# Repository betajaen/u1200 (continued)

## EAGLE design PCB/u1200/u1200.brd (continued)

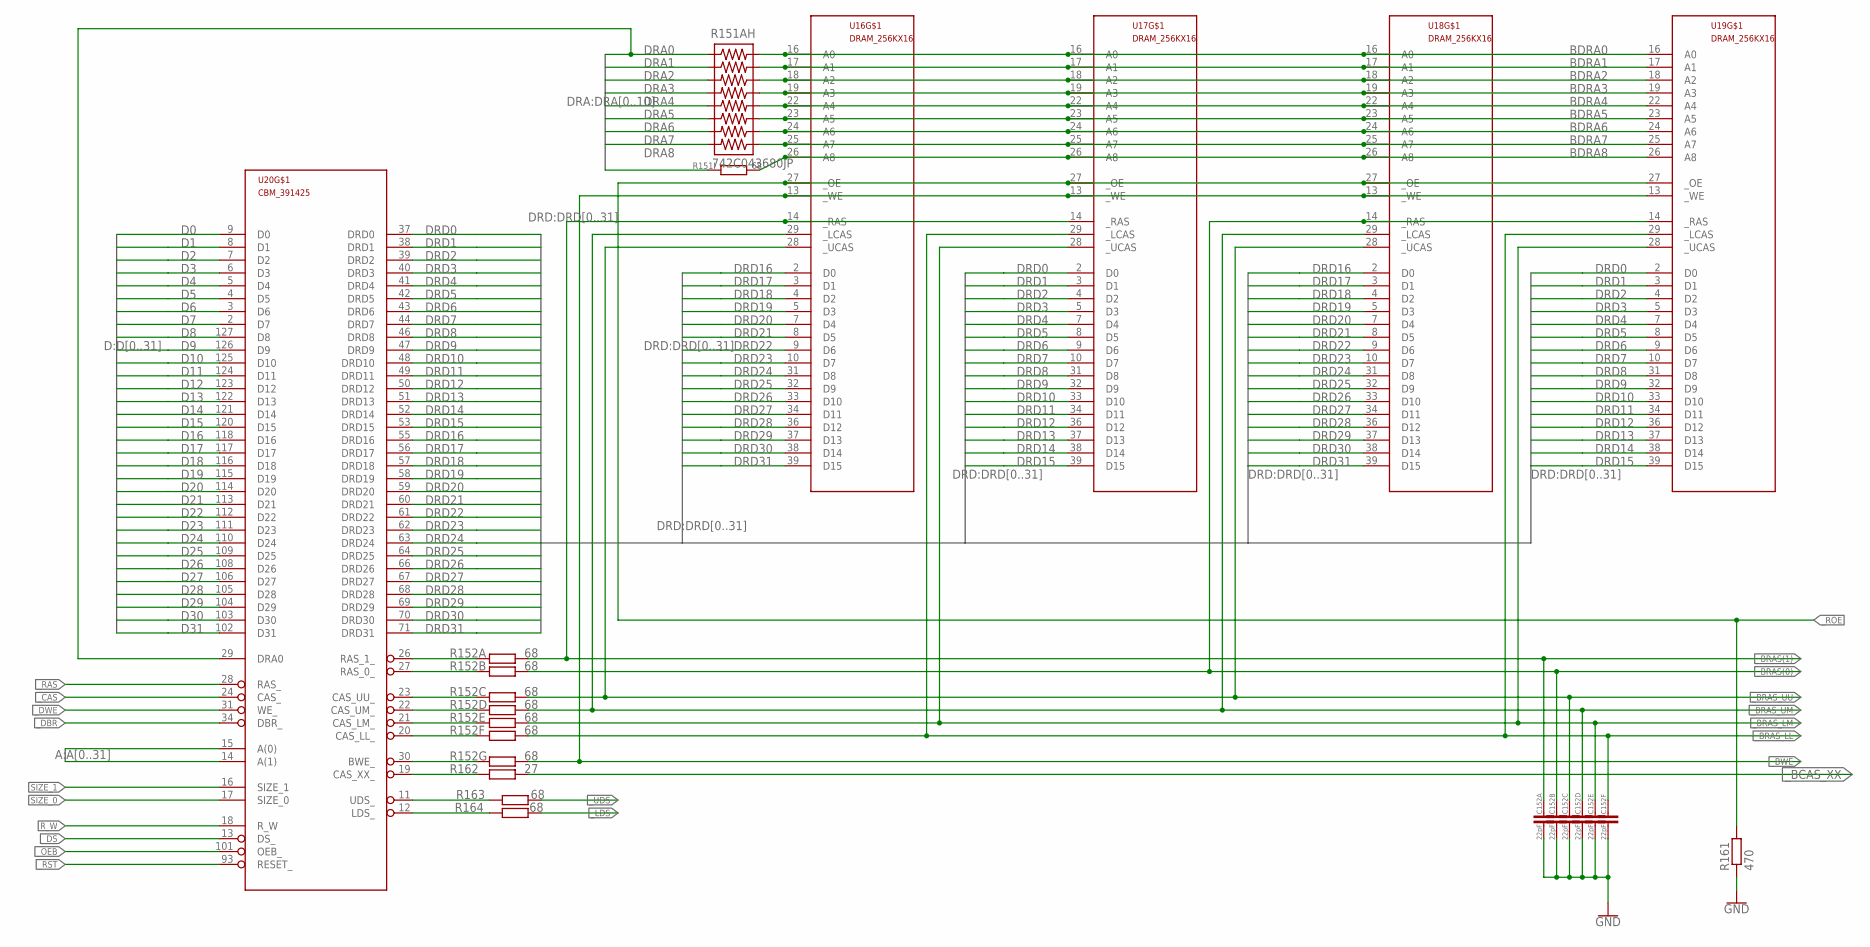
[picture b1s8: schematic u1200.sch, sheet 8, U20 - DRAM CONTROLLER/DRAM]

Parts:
C152A, C152B, C152C, C152D, C152E, C152F: 22pF; C0805
R151AH: 742C043680JP; 742C163220JP; MPN 742C043680JP; DIGIKEY_PARTNO 742C043680JPTR-ND
R151I: 68; R0603
R152A, R152B, R152C, R152D, R152E, R152F, R152G, R163, R164: 68; R0805
R161: 470; R0805
R162: 27; R0805
U16, U17, U18, U19: DRAM_256KX16; SOJ127P1117X376-40
U20: CBM_391425; SQFP-S-28X28-128

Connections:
A0: U20.15 (A(0)); also elsewhere on the board
A1: U20.14 (A(1)); also elsewhere on the board
BDRA0: R151AH.16, U16.16 (A0), U17.16 (A0), U18.16 (A0), U19.16 (A0)
BDRA1: R151AH.15, U16.17 (A1), U17.17 (A1), U18.17 (A1), U19.17 (A1)
BDRA2: R151AH.14, U16.18 (A2), U17.18 (A2), U18.18 (A2), U19.18 (A2)
BDRA3: R151AH.13, U16.19 (A3), U17.19 (A3), U18.19 (A3), U19.19 (A3)
BDRA4: R151AH.12, U16.22 (A4), U17.22 (A4), U18.22 (A4), U19.22 (A4)
BDRA5: R151AH.11, U16.23 (A5), U17.23 (A5), U18.23 (A5), U19.23 (A5)
BDRA6: R151AH.10, U16.24 (A6), U17.24 (A6), U18.24 (A6), U19.24 (A6)
BDRA7: R151AH.9, U16.25 (A7), U17.25 (A7), U18.25 (A7), U19.25 (A7)
BDRA8: R151I.2, U16.26 (A8), U17.26 (A8), U18.26 (A8), U19.26 (A8)
D0: U20.9 (D0); also elsewhere on the board
D1: U20.8 (D1); also elsewhere on the board
D2: U20.7 (D2); also elsewhere on the board
D3: U20.6 (D3); also elsewhere on the board
D4: U20.5 (D4); also elsewhere on the board
D5: U20.4 (D5); also elsewhere on the board
D6: U20.3 (D6); also elsewhere on the board
D7: U20.2 (D7); also elsewhere on the board
D8: U20.127 (D8); also elsewhere on the board
D9: U20.126 (D9); also elsewhere on the board
D10: U20.125 (D10); also elsewhere on the board
D11: U20.124 (D11); also elsewhere on the board
D12: U20.123 (D12); also elsewhere on the board
D13: U20.122 (D13); also elsewhere on the board
D14: U20.121 (D14); also elsewhere on the board
D15: U20.120 (D15); also elsewhere on the board
D16: U20.118 (D16); also elsewhere on the board
D17: U20.117 (D17); also elsewhere on the board
D18: U20.116 (D18); also elsewhere on the board
D19: U20.115 (D19); also elsewhere on the board
D20: U20.114 (D20); also elsewhere on the board
D21: U20.113 (D21); also elsewhere on the board
D22: U20.112 (D22); also elsewhere on the board
D23: U20.111 (D23); also elsewhere on the board
D24: U20.110 (D24); also elsewhere on the board
D25: U20.109 (D25); also elsewhere on the board
D26: U20.108 (D26); also elsewhere on the board
D27: U20.106 (D27); also elsewhere on the board
D28: U20.105 (D28); also elsewhere on the board
D29: U20.104 (D29); also elsewhere on the board
D30: U20.103 (D30); also elsewhere on the board
D31: U20.102 (D31); also elsewhere on the board
DRA0: R151AH.1, U20.29 (DRA0); also elsewhere on the board
DRA1: R151AH.2; also elsewhere on the board
DRA2: R151AH.3; also elsewhere on the board
DRA3: R151AH.4; also elsewhere on the board
DRA4: R151AH.5; also elsewhere on the board
DRA5: R151AH.6; also elsewhere on the board
DRA6: R151AH.7; also elsewhere on the board
DRA7: R151AH.8; also elsewhere on the board
DRA8: R151I.1; also elsewhere on the board
DRD0: U17.2 (D0), U19.2 (D0), U20.37 (DRD0); also elsewhere on the board
DRD1: U17.3 (D1), U19.3 (D1), U20.38 (DRD1); also elsewhere on the board
DRD2: U17.4 (D2), U19.4 (D2), U20.39 (DRD2); also elsewhere on the board
DRD3: U17.5 (D3), U19.5 (D3), U20.40 (DRD3); also elsewhere on the board
DRD4: U17.7 (D4), U19.7 (D4), U20.41 (DRD4); also elsewhere on the board
DRD5: U17.8 (D5), U19.8 (D5), U20.42 (DRD5); also elsewhere on the board
DRD6: U17.9 (D6), U19.9 (D6), U20.43 (DRD6); also elsewhere on the board
DRD7: U17.10 (D7), U19.10 (D7), U20.44 (DRD7); also elsewhere on the board
DRD8: U17.31 (D8), U19.31 (D8), U20.46 (DRD8); also elsewhere on the board
DRD9: U17.32 (D9), U19.32 (D9), U20.47 (DRD9); also elsewhere on the board
DRD10: U17.33 (D10), U19.33 (D10), U20.48 (DRD10); also elsewhere on the board
DRD11: U17.34 (D11), U19.34 (D11), U20.49 (DRD11); also elsewhere on the board
DRD12: U17.36 (D12), U19.36 (D12), U20.50 (DRD12); also elsewhere on the board
DRD13: U17.37 (D13), U19.37 (D13), U20.51 (DRD13); also elsewhere on the board
DRD14: U17.38 (D14), U19.38 (D14), U20.52 (DRD14); also elsewhere on the board
DRD15: U17.39 (D15), U19.39 (D15), U20.53 (DRD15); also elsewhere on the board
DRD16: U16.2 (D0), U18.2 (D0), U20.55 (DRD16); also elsewhere on the board
DRD17: U16.3 (D1), U18.3 (D1), U20.56 (DRD17); also elsewhere on the board
DRD18: U16.4 (D2), U18.4 (D2), U20.57 (DRD18); also elsewhere on the board
DRD19: U16.5 (D3), U18.5 (D3), U20.58 (DRD19); also elsewhere on the board
DRD20: U16.7 (D4), U18.7 (D4), U20.59 (DRD20); also elsewhere on the board
DRD21: U16.8 (D5), U18.8 (D5), U20.60 (DRD21); also elsewhere on the board
DRD22: U16.9 (D6), U18.9 (D6), U20.61 (DRD22); also elsewhere on the board
DRD23: U16.10 (D7), U18.10 (D7), U20.62 (DRD23); also elsewhere on the board
DRD24: U16.31 (D8), U18.31 (D8), U20.63 (DRD24); also elsewhere on the board
DRD25: U16.32 (D9), U18.32 (D9), U20.64 (DRD25); also elsewhere on the board
DRD26: U16.33 (D10), U18.33 (D10), U20.66 (DRD26); also elsewhere on the board
DRD27: U16.34 (D11), U18.34 (D11), U20.67 (DRD27); also elsewhere on the board
DRD28: U16.36 (D12), U18.36 (D12), U20.68 (DRD28); also elsewhere on the board
DRD29: U16.37 (D13), U18.37 (D13), U20.69 (DRD29); also elsewhere on the board
DRD30: U16.38 (D14), U18.38 (D14), U20.70 (DRD30); also elsewhere on the board
DRD31: U16.39 (D15), U18.39 (D15), U20.71 (DRD31); also elsewhere on the board
GND: C152A.2, C152B.2, C152C.2, C152D.2, C152E.2, C152F.2, R161.1; also elsewhere on the board
GND1: U16.35 (GND1), U17.35 (GND1), U18.35 (GND1), U19.35 (GND1)
GND2: U16.40 (GND2), U17.40 (GND2), U18.40 (GND2), U19.40 (GND2)
unnamed: R152G.1, U20.30 (BWE_)
unnamed: R163.1, U20.11 (UDS_)
unnamed: R164.1, U20.12 (LDS_)
unnamed: R162.1, U20.19 (CAS_XX_)
unnamed: R152F.1, U20.20 (CAS_LL_)
unnamed: R152E.1, U20.21 (CAS_LM_)
unnamed: R152D.1, U20.22 (CAS_UM_)
unnamed: R152C.1, U20.23 (CAS_UU_)
unnamed: R152B.1, U20.27 (RAS_0_)
unnamed: R152A.1, U20.26 (RAS_1_)
R_W: U20.18 (R_W); also elsewhere on the board
SIZE_0: U20.17 (SIZE_0); also elsewhere on the board
SIZE_1: U20.16 (SIZE_1); also elsewhere on the board
VCC0: U16.1 (VCC0), U17.1 (VCC0), U18.1 (VCC0), U19.1 (VCC0)
VCC1: U16.6 (VCC1), U17.6 (VCC1), U18.6 (VCC1), U19.6 (VCC1); also elsewhere on the board
VCC2: U16.20 (VCC2), U17.20 (VCC2), U18.20 (VCC2), U19.20 (VCC2); also elsewhere on the board
_BCAS_XX: R162.2; also elsewhere on the board
_BRAS(0): C152B.1, R152B.2, U18.14 (_RAS), U19.14 (_RAS)
_BRAS(1): C152A.1, R152A.2, U16.14 (_RAS), U17.14 (_RAS)
_BRAS_LL: C152F.1, R152F.2, U17.29 (_LCAS), U19.29 (_LCAS)
_BRAS_LM: C152E.1, R152E.2, U17.28 (_UCAS), U19.28 (_UCAS)
_BRAS_UM: C152D.1, R152D.2, U16.29 (_LCAS), U18.29 (_LCAS)
_BRAS_UU: C152C.1, R152C.2, U16.28 (_UCAS), U18.28 (_UCAS)
_BWE: R152G.2, U16.13 (_WE), U17.13 (_WE), U18.13 (_WE), U19.13 (_WE)
_CAS: U20.24 (CAS_); also elsewhere on the board
_DBR: U20.34 (DBR_); also elsewhere on the board
_DS: U20.13 (DS_); also elsewhere on the board
_DWE: U20.31 (WE_)
_LDS: R164.2
_OEB: U20.101 (OEB_)
_RAS: U20.28 (RAS_); also elsewhere on the board
_ROE: R161.2, U16.27 (_OE), U17.27 (_OE), U18.27 (_OE), U19.27 (_OE)
_RST: U20.93 (RESET_); also elsewhere on the board
_UDS: R163.2

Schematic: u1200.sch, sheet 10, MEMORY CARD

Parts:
U20: CBM_391425; SQFP-S-28X28-128

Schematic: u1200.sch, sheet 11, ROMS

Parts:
R593: 470**; R0603
U6A, U6B: CBM_A1200_ROM_U6AB; CBM_A1200_ROM_DIL42

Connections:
A2: U6A.10 (A0), U6B.10 (A0); also elsewhere on the board
A3: U6A.9 (A1), U6B.9 (A1); also elsewhere on the board
A4: U6A.8 (A2), U6B.8 (A2); also elsewhere on the board
A5: U6A.7 (A3), U6B.7 (A3); also elsewhere on the board
A6: U6A.6 (A4), U6B.6 (A4); also elsewhere on the board
A7: U6A.5 (A5), U6B.5 (A5); also elsewhere on the board
A8: U6A.4 (A6), U6B.4 (A6); also elsewhere on the board
A9: U6A.3 (A7), U6B.3 (A7); also elsewhere on the board
A10: U6A.41 (A8), U6B.41 (A8); also elsewhere on the board
A11: U6A.40 (A9), U6B.40 (A9); also elsewhere on the board
A12: U6A.39 (A10), U6B.39 (A10); also elsewhere on the board
A13: U6A.38 (A11), U6B.38 (A11); also elsewhere on the board
A14: U6A.37 (A12), U6B.37 (A12); also elsewhere on the board
A15: U6A.36 (A13), U6B.36 (A13); also elsewhere on the board
A16: U6A.35 (A14), U6B.35 (A14); also elsewhere on the board
A17: U6A.34 (A15), U6B.34 (A15); also elsewhere on the board
A18: U6A.33 (A16), U6B.33 (A16); also elsewhere on the board
D0: U6B.14 (D0); also elsewhere on the board
D1: U6B.16 (D1); also elsewhere on the board
D2: U6B.18 (D2); also elsewhere on the board
D3: U6B.20 (D3); also elsewhere on the board
D4: U6B.23 (D4); also elsewhere on the board
D5: U6B.25 (D5); also elsewhere on the board
D6: U6B.27 (D6); also elsewhere on the board
D7: U6B.29 (D7); also elsewhere on the board
D8: U6B.15 (D8); also elsewhere on the board
D9: U6B.17 (D9); also elsewhere on the board
D10: U6B.19 (D10); also elsewhere on the board
D11: U6B.21 (D11); also elsewhere on the board
D12: U6B.24 (D12); also elsewhere on the board
D13: U6B.26 (D13); also elsewhere on the board
D14: U6B.28 (D14); also elsewhere on the board
D15: U6B.30 (A-1/D16); also elsewhere on the board
D16: U6A.14 (D0); also elsewhere on the board
D17: U6A.16 (D1); also elsewhere on the board
D18: U6A.18 (D2); also elsewhere on the board
D19: U6A.20 (D3); also elsewhere on the board
D20: U6A.23 (D4); also elsewhere on the board
D21: U6A.25 (D5); also elsewhere on the board
D22: U6A.27 (D6); also elsewhere on the board
D23: U6A.29 (D7); also elsewhere on the board
D24: U6A.15 (D8); also elsewhere on the board
D25: U6A.17 (D9); also elsewhere on the board
D26: U6A.19 (D10); also elsewhere on the board
D27: U6A.21 (D11); also elsewhere on the board
D28: U6A.24 (D12); also elsewhere on the board
D29: U6A.26 (D13); also elsewhere on the board
D30: U6A.28 (D14); also elsewhere on the board
D31: U6A.30 (A-1/D16); also elsewhere on the board
GND: U6A.12 (VSS), U6A.31 (VSS), U6B.12 (VSS), U6B.31 (VSS); also elsewhere on the board
VCC: U6A.22 (VCC), U6A.32 (BYTE), U6B.22 (VCC), U6B.32 (BYTE); also elsewhere on the board
_OE: U6A.13 (OE), U6B.13 (OE); also elsewhere on the board
_ROMEN: R593.2, U6A.11 (CE), U6B.11 (CE)
_WIDE: R593.1; also elsewhere on the board

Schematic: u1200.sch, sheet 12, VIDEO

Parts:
E132C: *; C0805
E132R, E375R, E376R, E377R: 68; R0805
E375C, E376C, E377C: 22pF; C0805
U4: CBM_4203; PLCC84-SMD-AMP-SOCKED

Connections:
14MHZ: E377C.2, E377R.1, E377R.2, U4.23 (C140); also elsewhere on the board
C28M: U4.25 (C28M)
CCK: U4.10 (CCK); also elsewhere on the board
DRD0: U4.8 (D0); also elsewhere on the board
DRD1: U4.7 (D1); also elsewhere on the board
DRD2: U4.6 (D2); also elsewhere on the board
DRD3: U4.5 (D3); also elsewhere on the board
DRD4: U4.4 (D4); also elsewhere on the board
DRD5: U4.3 (D5); also elsewhere on the board
DRD6: U4.2 (D6); also elsewhere on the board
DRD7: U4.84 (D7); also elsewhere on the board
DRD8: U4.82 (D8); also elsewhere on the board
DRD9: U4.81 (D9); also elsewhere on the board
DRD10: U4.80 (D10); also elsewhere on the board
DRD11: U4.79 (D11); also elsewhere on the board
DRD12: U4.78 (D12); also elsewhere on the board
DRD13: U4.77 (D13); also elsewhere on the board
DRD14: U4.76 (D14); also elsewhere on the board
DRD15: U4.75 (D15); also elsewhere on the board
DRD16: U4.74 (D16); also elsewhere on the board
DRD17: U4.73 (D17); also elsewhere on the board
DRD18: U4.72 (D18); also elsewhere on the board
DRD19: U4.71 (D19); also elsewhere on the board
DRD20: U4.70 (D20); also elsewhere on the board
DRD21: U4.69 (D21); also elsewhere on the board
DRD22: U4.68 (D22); also elsewhere on the board
DRD23: U4.67 (D23); also elsewhere on the board
DRD24: U4.66 (D24); also elsewhere on the board
DRD25: U4.65 (D25); also elsewhere on the board
DRD26: U4.64 (D26); also elsewhere on the board
DRD27: U4.63 (D27); also elsewhere on the board
DRD28: U4.62 (D28); also elsewhere on the board
DRD29: U4.61 (D29); also elsewhere on the board
DRD30: U4.60 (D30); also elsewhere on the board
DRD31: U4.59 (D31); also elsewhere on the board
GND: E132C.2, E375C.1, E376C.1, E377C.1; also elsewhere on the board
MDAT: U4.20 (MDAT)
unnamed: E375R.2, U4.21 (_MLD)
unnamed: E132R.1, U4.43 (C280)
unnamed: E376R.2, U4.22 (SCLK)
RGA1: U4.19 (RGA1); also elsewhere on the board
RGA2: U4.18 (RGA2); also elsewhere on the board
RGA3: U4.17 (RGA3); also elsewhere on the board
RGA4: U4.16 (RGA4); also elsewhere on the board
RGA5: U4.15 (RGA5); also elsewhere on the board
RGA6: U4.14 (RGA6); also elsewhere on the board
RGA7: U4.13 (RGA7); also elsewhere on the board
RGA8: U4.12 (RGA8); also elsewhere on the board
SCLK: E376C.2, E376R.1; also elsewhere on the board
XC280: E132C.1, E132R.2; also elsewhere on the board
XSOG: U4.26 (SOG); also elsewhere on the board
XZD: U4.28 (ZD); also elsewhere on the board
_BCAS_XX: U4.9 (_CAS); also elsewhere on the board
_MLD: E375C.2, E375R.1
_RST: U4.24 (_RST); also elsewhere on the board
_XBLANK: U4.27 (BLANK); also elsewhere on the board
_XRGB0: U4.48 (R0); also elsewhere on the board
_XRGB1: U4.49 (R1); also elsewhere on the board
_XRGB2: U4.50 (R2); also elsewhere on the board
_XRGB3: U4.51 (R3); also elsewhere on the board
_XRGB4: U4.52 (R4); also elsewhere on the board
_XRGB5: U4.54 (R5); also elsewhere on the board
_XRGB6: U4.55 (R6); also elsewhere on the board
_XRGB7: U4.57 (R7); also elsewhere on the board
_XRGB8: U4.39 (G0); also elsewhere on the board
_XRGB9: U4.40 (G1); also elsewhere on the board
_XRGB10: U4.41 (G2); also elsewhere on the board
_XRGB11: U4.42 (G3); also elsewhere on the board
_XRGB12: U4.44 (G4); also elsewhere on the board
_XRGB13: U4.45 (G5); also elsewhere on the board
_XRGB14: U4.46 (G6); also elsewhere on the board
_XRGB15: U4.47 (G7); also elsewhere on the board
_XRGB16: U4.29 (B0); also elsewhere on the board
_XRGB17: U4.31 (B1); also elsewhere on the board
_XRGB18: U4.32 (B2); also elsewhere on the board
_XRGB19: U4.34 (B3); also elsewhere on the board
_XRGB20: U4.35 (B4); also elsewhere on the board
_XRGB21: U4.36 (B5); also elsewhere on the board
_XRGB22: U4.37 (B6); also elsewhere on the board
_XRGB23: U4.38 (B7); also elsewhere on the board

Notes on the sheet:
E375
E376
E377
E132

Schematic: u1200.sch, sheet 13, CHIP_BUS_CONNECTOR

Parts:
XP1, XP2, XP3: U1200_CHIP_BUS_CONNECTOR; 145167-2

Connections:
+12V: XP1.1 (+12V), XP2.1 (+12V), XP3.1 (+12V); also elsewhere on the board
-12V: XP1.2 (-12V), XP2.2 (-12V), XP3.2 (-12V); also elsewhere on the board
DRD0: XP1.3 (DRD0), XP2.3 (DRD0), XP3.3 (DRD0); also elsewhere on the board
DRD1: XP1.4 (DRD1), XP2.4 (DRD1), XP3.4 (DRD1); also elsewhere on the board
DRD2: XP1.5 (DRD2), XP2.5 (DRD2), XP3.5 (DRD2); also elsewhere on the board
DRD3: XP1.6 (DRD3), XP2.6 (DRD3), XP3.6 (DRD3); also elsewhere on the board
DRD4: XP1.7 (DRD4), XP2.7 (DRD4), XP3.7 (DRD4); also elsewhere on the board
DRD5: XP1.8 (DRD5), XP2.8 (DRD5), XP3.8 (DRD5); also elsewhere on the board
DRD6: XP1.9 (DRD6), XP2.9 (DRD6), XP3.9 (DRD6); also elsewhere on the board
DRD7: XP1.10 (DRD7), XP2.10 (DRD7), XP3.10 (DRD7); also elsewhere on the board
DRD8: XP1.11 (DRD8), XP2.11 (DRD8), XP3.11 (DRD8); also elsewhere on the board
DRD9: XP1.12 (DRD9), XP2.12 (DRD9), XP3.12 (DRD9); also elsewhere on the board
DRD10: XP1.13 (DRD10), XP2.13 (DRD10), XP3.13 (DRD10); also elsewhere on the board
DRD11: XP1.14 (DRD11), XP2.14 (DRD11), XP3.14 (DRD11); also elsewhere on the board
DRD12: XP1.15 (DRD12), XP2.15 (DRD12), XP3.15 (DRD12); also elsewhere on the board
DRD13: XP1.16 (DRD13), XP2.16 (DRD13), XP3.16 (DRD13); also elsewhere on the board
DRD14: XP1.17 (DRD14), XP2.17 (DRD14), XP3.17 (DRD14); also elsewhere on the board
DRD15: XP1.18 (DRD15), XP2.18 (DRD15), XP3.18 (DRD15); also elsewhere on the board
DRD16: XP1.19 (DRD16), XP2.19 (DRD16), XP3.19 (DRD16); also elsewhere on the board
DRD17: XP1.20 (DRD17), XP2.20 (DRD17), XP3.20 (DRD17); also elsewhere on the board
DRD18: XP1.21 (DRD18), XP2.21 (DRD18), XP3.21 (DRD18); also elsewhere on the board
DRD19: XP1.22 (DRD19), XP2.22 (DRD19), XP3.22 (DRD19); also elsewhere on the board
DRD20: XP1.23 (DRD20), XP2.23 (DRD20), XP3.23 (DRD20); also elsewhere on the board
DRD21: XP1.24 (DRD21), XP2.24 (DRD21), XP3.24 (DRD21); also elsewhere on the board
DRD22: XP1.25 (DRD22), XP2.25 (DRD22), XP3.25 (DRD22); also elsewhere on the board
DRD23: XP1.26 (DRD23), XP2.26 (DRD23), XP3.26 (DRD23); also elsewhere on the board
DRD24: XP1.27 (DRD24), XP2.27 (DRD24), XP3.27 (DRD24); also elsewhere on the board
DRD25: XP1.28 (DRD25), XP2.28 (DRD25), XP3.28 (DRD25); also elsewhere on the board
DRD26: XP1.29 (DRD26), XP2.29 (DRD26), XP3.29 (DRD26); also elsewhere on the board
DRD27: XP1.30 (DRD27), XP2.30 (DRD27), XP3.30 (DRD27); also elsewhere on the board
DRD28: XP1.31 (DRD28), XP2.31 (DRD28), XP3.31 (DRD28); also elsewhere on the board
DRD29: XP1.32 (DRD29), XP2.32 (DRD29), XP3.32 (DRD29); also elsewhere on the board
DRD30: XP1.33 (DRD30), XP2.33 (DRD30), XP3.33 (DRD30); also elsewhere on the board
DRD31: XP1.34 (DRD31), XP2.34 (DRD31), XP3.34 (DRD31); also elsewhere on the board
GND: XP1.35 (GND), XP2.35 (GND), XP3.35 (GND); also elsewhere on the board
RGA1: XP1.36 (RGA1), XP2.36 (RGA1), XP3.36 (RGA1); also elsewhere on the board
RGA2: XP1.37 (RGA2), XP2.37 (RGA2), XP3.37 (RGA2); also elsewhere on the board
RGA3: XP1.38 (RGA3), XP2.38 (RGA3), XP3.38 (RGA3); also elsewhere on the board
RGA4: XP1.39 (RGA4), XP2.39 (RGA4), XP3.39 (RGA4); also elsewhere on the board
RGA5: XP1.40 (RGA5), XP2.40 (RGA5), XP3.40 (RGA5); also elsewhere on the board
RGA6: XP1.41 (RGA6), XP2.41 (RGA6), XP3.41 (RGA6); also elsewhere on the board
RGA7: XP1.42 (RGA7), XP2.42 (RGA7), XP3.42 (RGA7); also elsewhere on the board
RGA8: XP1.43 (RGA8), XP2.43 (RGA8), XP3.43 (RGA8); also elsewhere on the board
VCC: XP1.44 (VCC), XP2.44 (VCC), XP3.44 (VCC); also elsewhere on the board
XC280: XP1.54 (C280), XP2.54 (C280), XP3.54 (C280); also elsewhere on the board
XSOG: XP1.73 (SOG), XP2.73 (SOG), XP3.73 (SOG); also elsewhere on the board
XZD: XP1.75 (ZD), XP2.75 (ZD), XP3.75 (ZD); also elsewhere on the board
_CSYNC: XP1.55 (CSYNC), XP2.55 (CSYNC), XP3.55 (CSYNC); also elsewhere on the board
_HSYNC: XP1.64 (HSYNC), XP2.64 (HSYNC), XP3.64 (HSYNC); also elsewhere on the board
_VSYNC: XP1.74 (VSYNC), XP2.74 (VSYNC), XP3.74 (VSYNC); also elsewhere on the board
_XBLANK: XP1.53 (BLANK), XP2.53 (BLANK), XP3.53 (BLANK); also elsewhere on the board
_XRGB0: XP1.65 (R0), XP2.65 (R0), XP3.65 (R0); also elsewhere on the board
_XRGB1: XP1.66 (R1), XP2.66 (R1), XP3.66 (R1); also elsewhere on the board
_XRGB2: XP1.67 (R2), XP2.67 (R2), XP3.67 (R2); also elsewhere on the board
_XRGB3: XP1.68 (R3), XP2.68 (R3), XP3.68 (R3); also elsewhere on the board
_XRGB4: XP1.69 (R4), XP2.69 (R4), XP3.69 (R4); also elsewhere on the board
_XRGB5: XP1.70 (R5), XP2.70 (R5), XP3.70 (R5); also elsewhere on the board
_XRGB6: XP1.71 (R6), XP2.71 (R6), XP3.71 (R6); also elsewhere on the board
_XRGB7: XP1.72 (R7), XP2.72 (R7), XP3.72 (R7); also elsewhere on the board
_XRGB8: XP1.56 (G0), XP2.56 (G0), XP3.56 (G0); also elsewhere on the board
_XRGB9: XP1.57 (G1), XP2.57 (G1), XP3.57 (G1); also elsewhere on the board
_XRGB10: XP1.58 (G2), XP2.58 (G2), XP3.58 (G2); also elsewhere on the board
_XRGB11: XP1.59 (G3), XP2.59 (G3), XP3.59 (G3); also elsewhere on the board
_XRGB12: XP1.60 (G4), XP2.60 (G4), XP3.60 (G4); also elsewhere on the board
_XRGB13: XP1.61 (G5), XP2.61 (G5), XP3.61 (G5); also elsewhere on the board
_XRGB14: XP1.62 (G6), XP2.62 (G6), XP3.62 (G6); also elsewhere on the board
_XRGB15: XP1.63 (G7), XP2.63 (G7), XP3.63 (G7); also elsewhere on the board
_XRGB16: XP1.45 (B0), XP2.45 (B0), XP3.45 (B0); also elsewhere on the board
_XRGB17: XP1.46 (B1), XP2.46 (B1), XP3.46 (B1); also elsewhere on the board
_XRGB18: XP1.47 (B2), XP2.47 (B2), XP3.47 (B2); also elsewhere on the board
_XRGB19: XP1.48 (B3), XP2.48 (B3), XP3.48 (B3); also elsewhere on the board
_XRGB20: XP1.49 (B4), XP2.49 (B4), XP3.49 (B4); also elsewhere on the board
_XRGB21: XP1.50 (B5), XP2.50 (B5), XP3.50 (B5); also elsewhere on the board
_XRGB22: XP1.51 (B6), XP2.51 (B6), XP3.51 (B6); also elsewhere on the board
_XRGB23: XP1.52 (B7), XP2.52 (B7), XP3.52 (B7); also elsewhere on the board

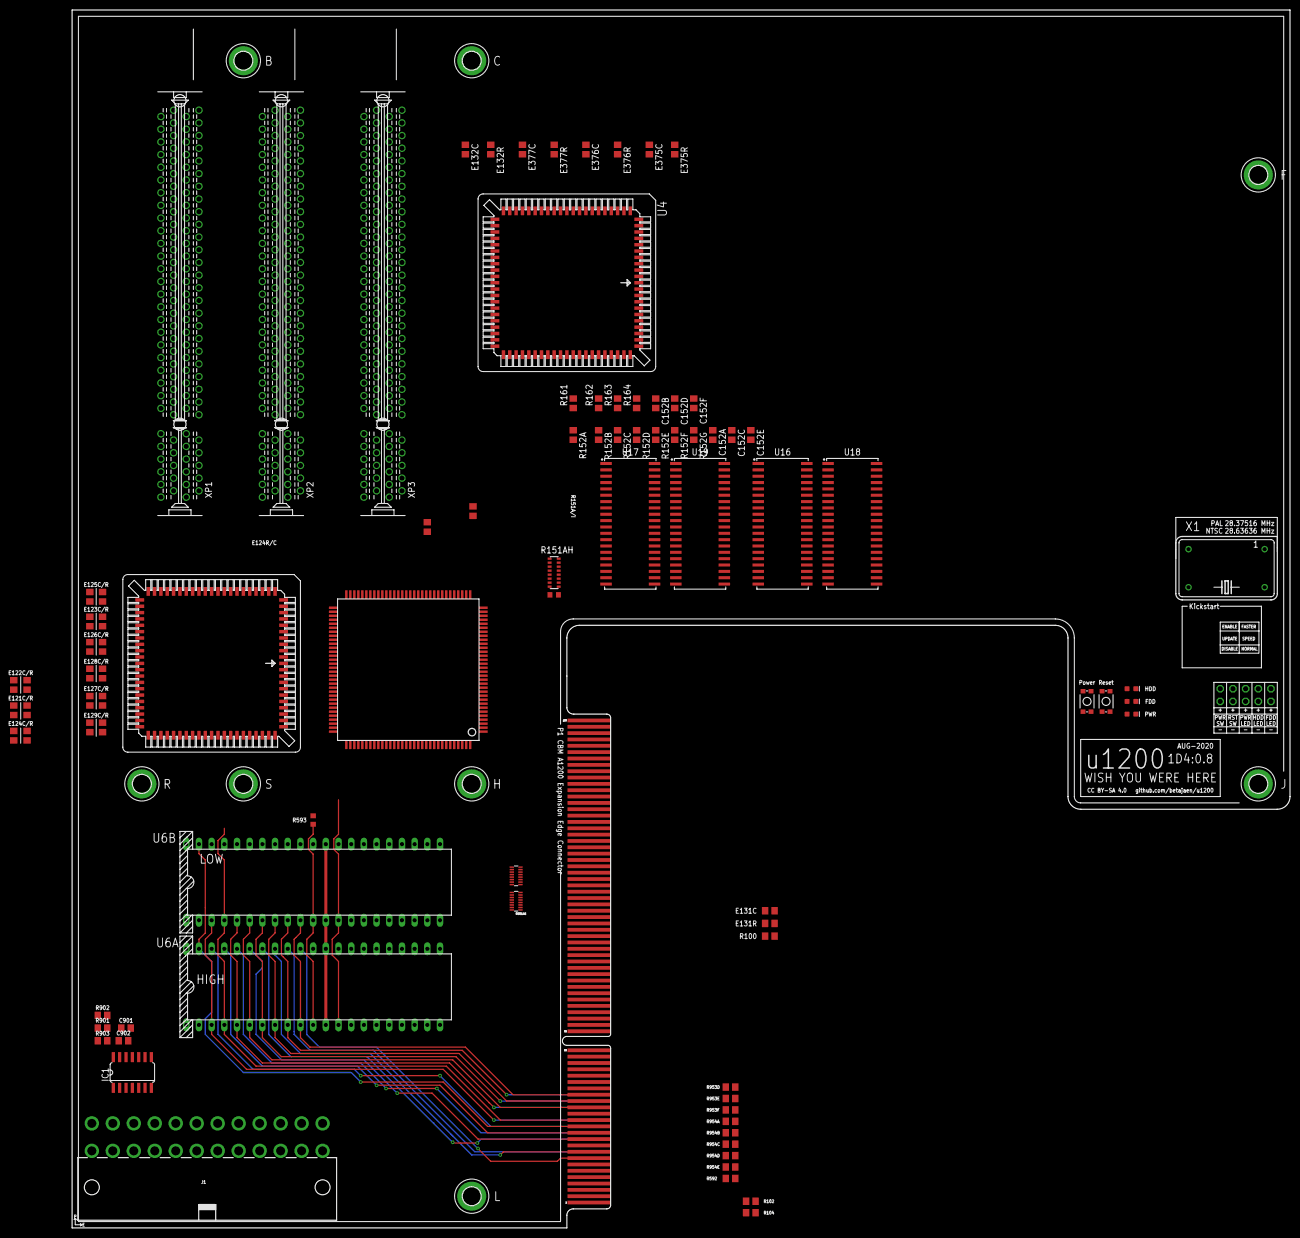
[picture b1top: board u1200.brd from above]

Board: 2 copper layers, 243.8 x 243.8 mm, 100 parts (0 on the bottom side), 226 nets.

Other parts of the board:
U$1: REF_P5_A1200_PPC_040

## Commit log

2020-08-08 Added in Shape, Edge Connector, ROMs, Power, Bus Controllers, Chip Mem, Video IC and Expansion Bus
2020-08-08 Datasheets/Notes
2020-08-08 A and DRA bus manual routing
2020-08-09 a0-a20 bus from edge connector to chip ram
2020-08-09 a0-a120 chipram/edge connector bus moved to top layer
2020-08-09 Added License
2020-08-22 Changed ROMs more traditional format. Re-routed A bus
